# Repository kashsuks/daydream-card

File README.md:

# daydream-card
Daydream Ottawa's PCB Hacker Card!

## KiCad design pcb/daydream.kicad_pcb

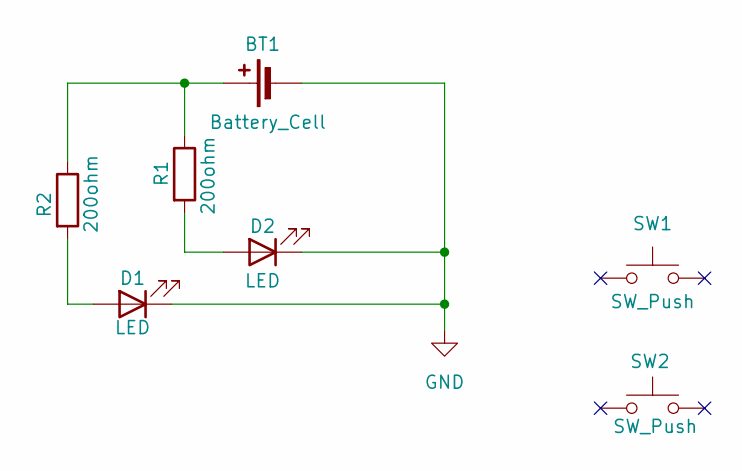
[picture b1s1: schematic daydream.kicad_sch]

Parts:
BT1: Battery_Cell; BatteryHolder_Keystone_3000_1x12mm
D1, D2: LED; LED_D5.0mm
R1, R2: 200ohm; R_Axial_DIN0207_L6.3mm_D2.5mm_P7.62mm_Horizontal
SW1, SW2: SW_Push; SW_PUSH_6mm_H5mm

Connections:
GND: BT1.2 (-), D1.1 (K), D2.1 (K)
unnamed: BT1.1 (+), R1.1, R2.1
unnamed: D1.2 (A), R2.2
unnamed: D2.2 (A), R1.2

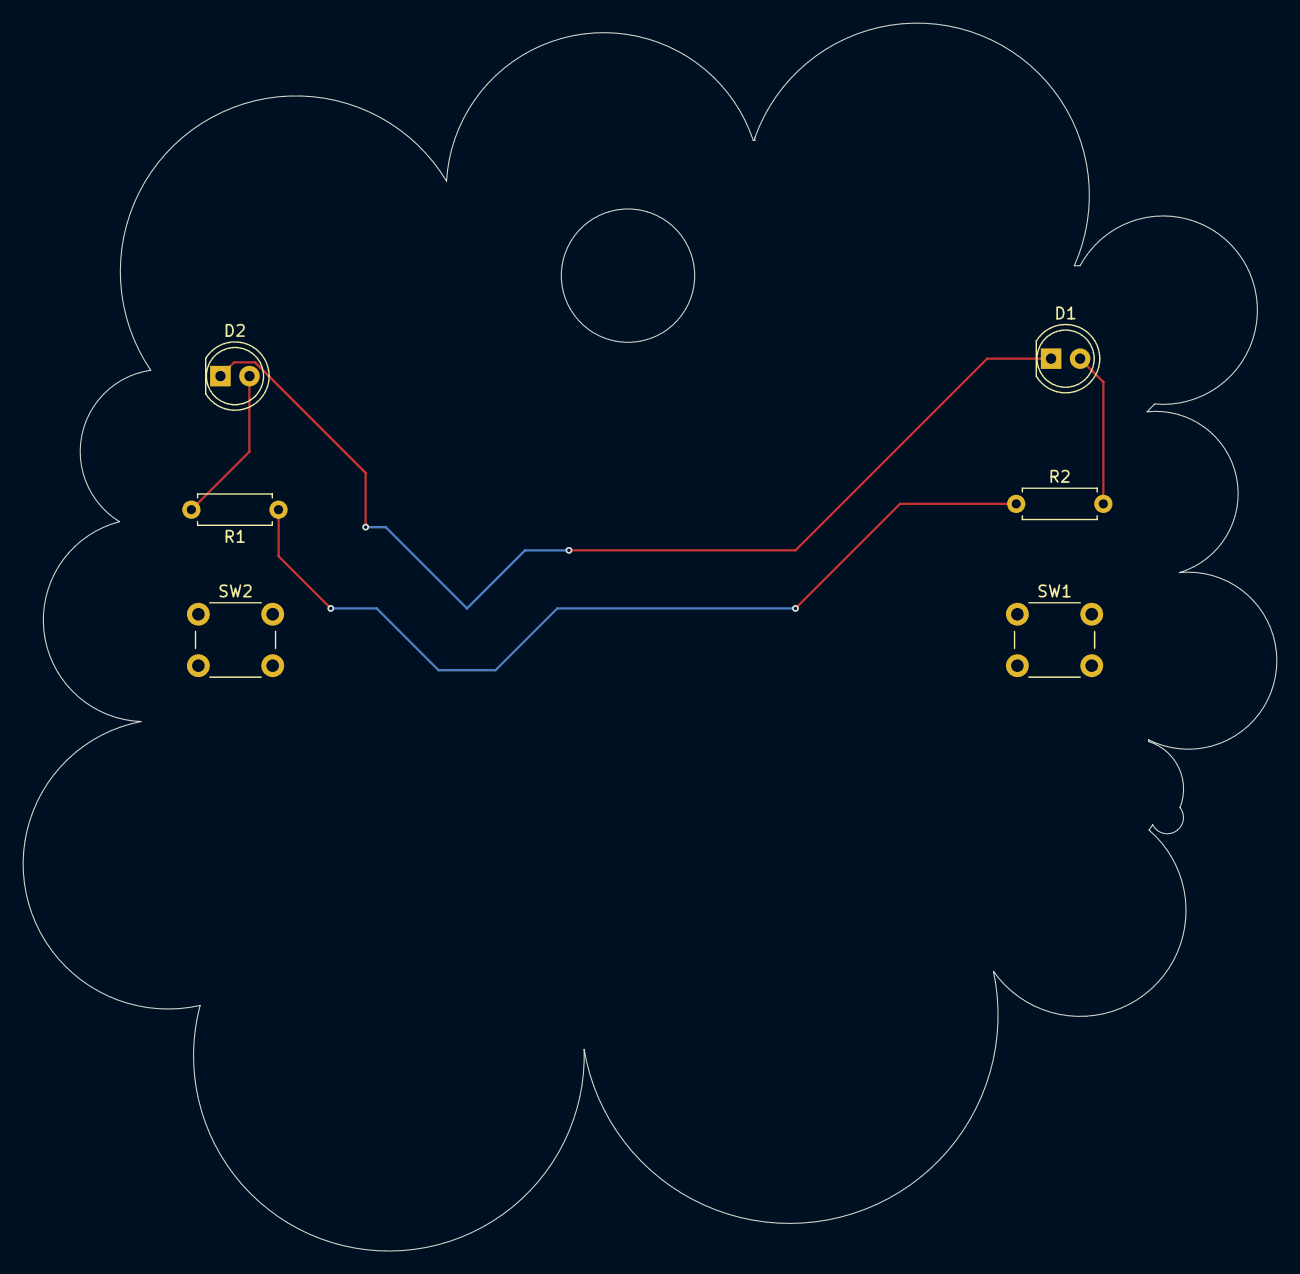
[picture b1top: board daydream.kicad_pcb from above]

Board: 2 copper layers, 109.6 x 107.4 mm, 7 parts (1 on the bottom side), 4 nets.

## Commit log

2025-07-18 Create something
2025-07-30 added battery
2025-07-30 finished the schematic
2025-07-30 added uhh a lot of stuff
